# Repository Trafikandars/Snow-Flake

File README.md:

# Snow-Flake
Machine à Neige DMX pour le Theâtre - DMX Snow Flake Machine for theater

Ce projet vous est proposé par la compagnie Trafikandars :

C'est une machine permettant de lâcher des cotillons ou autre, contrôlable en DMX.
La construction nécessite des pièces imprimées en 3D et un circuit imprimé sur mesure. 
Tous les fichiers sont disponibles ici pour que vous puissiez la faire vous-même. 
Si vous n’avez pas le matériel nous vous proposons de vous envoyer un kit contenant tous les éléments nécessaire à son assemblage pour la monter ou de vous l’envoyer prête à l’usage.
Si vous trouvez des pistes d'améliorations je reste ouvert à toute requet : Trafikandars.workshop@gmail.com

Conception 3D : Adem Koanda_Saurel

Code : Côme Douville

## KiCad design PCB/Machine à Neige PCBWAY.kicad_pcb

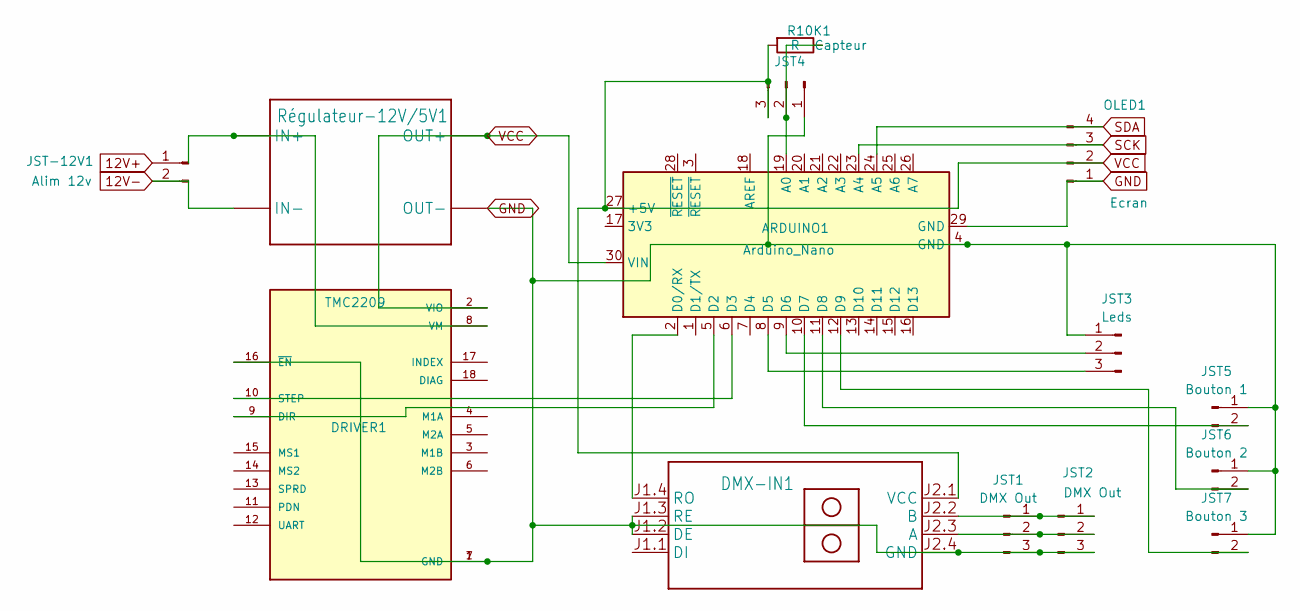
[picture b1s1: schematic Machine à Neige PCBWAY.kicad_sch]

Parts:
ARDUINO1: Arduino_Nano
DMX-IN1: RS485-TTL-CONVERTER
DRIVER1: TMC2209; MODULE_TMC2209_SILENTSTEPSTICK; PARTREV 1.20
JST1, JST2: DMX Out; PinSocket_1x03_P2.54mm_Vertical
JST3: Leds; PinSocket_1x03_P2.54mm_Vertical
JST4: Capteur; PinSocket_1x03_P2.54mm_Vertical
JST5: Bouton 1; PinSocket_1x02_P2.54mm_Vertical
JST6: Bouton 2; PinSocket_1x02_P2.54mm_Vertical
JST7: Bouton 3; PinSocket_1x02_P2.54mm_Vertical
JST-12V1: Alim 12v; PinSocket_1x02_P2.54mm_Vertical
OLED1: Ecran; PinSocket_1x04_P2.54mm_Vertical
R10K1: R; R_Axial_DIN0207_L6.3mm_D2.5mm_P5.08mm_Vertical
Régulateur-12V/5V1: StepDown-lm2596

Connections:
12V+: JST-12V1.1
12V-: JST-12V1.2, Régulateur-12V/5V1.2 (IN-)
GND: ARDUINO1.4 (GND), ARDUINO1.29 (GND), DMX-IN1.J1.2 (DE), DMX-IN1.J1.3 (RE), DMX-IN1.J2.4 (GND), DRIVER1.1 (GND), DRIVER1.7 (GND), DRIVER1.16 (~EN), JST1.3, JST2.3, JST3.1, JST4.1, JST5.1, JST6.1, JST7.1, OLED1.1, Régulateur-12V/5V1.4 (OUT-)
unnamed: ARDUINO1.19 (A0), JST4.2, R10K1.1
unnamed: ARDUINO1.2 (D0/RX), DMX-IN1.J1.4 (RO)
unnamed: ARDUINO1.5 (D2), DRIVER1.9 (DIR)
unnamed: ARDUINO1.6 (D3), DRIVER1.10 (STEP)
unnamed: ARDUINO1.8 (D5), JST3.3
unnamed: ARDUINO1.9 (D6), JST3.2
unnamed: ARDUINO1.10 (D7), JST5.2
unnamed: ARDUINO1.11 (D8), JST6.2
unnamed: ARDUINO1.12 (D9), JST7.2
unnamed: DMX-IN1.J2.3 (A), JST1.2, JST2.2
unnamed: DMX-IN1.J2.2 (B), JST1.1, JST2.1
unnamed: DRIVER1.8 (VM), Régulateur-12V/5V1.1 (IN+)
SCK: ARDUINO1.23 (A4), OLED1.3
SDA: ARDUINO1.24 (A5), OLED1.4
VCC: ARDUINO1.27 (+5V), ARDUINO1.30 (VIN), DMX-IN1.J2.1 (VCC), DRIVER1.2 (VIO), JST4.3, OLED1.2, R10K1.2, Régulateur-12V/5V1.3 (OUT+)

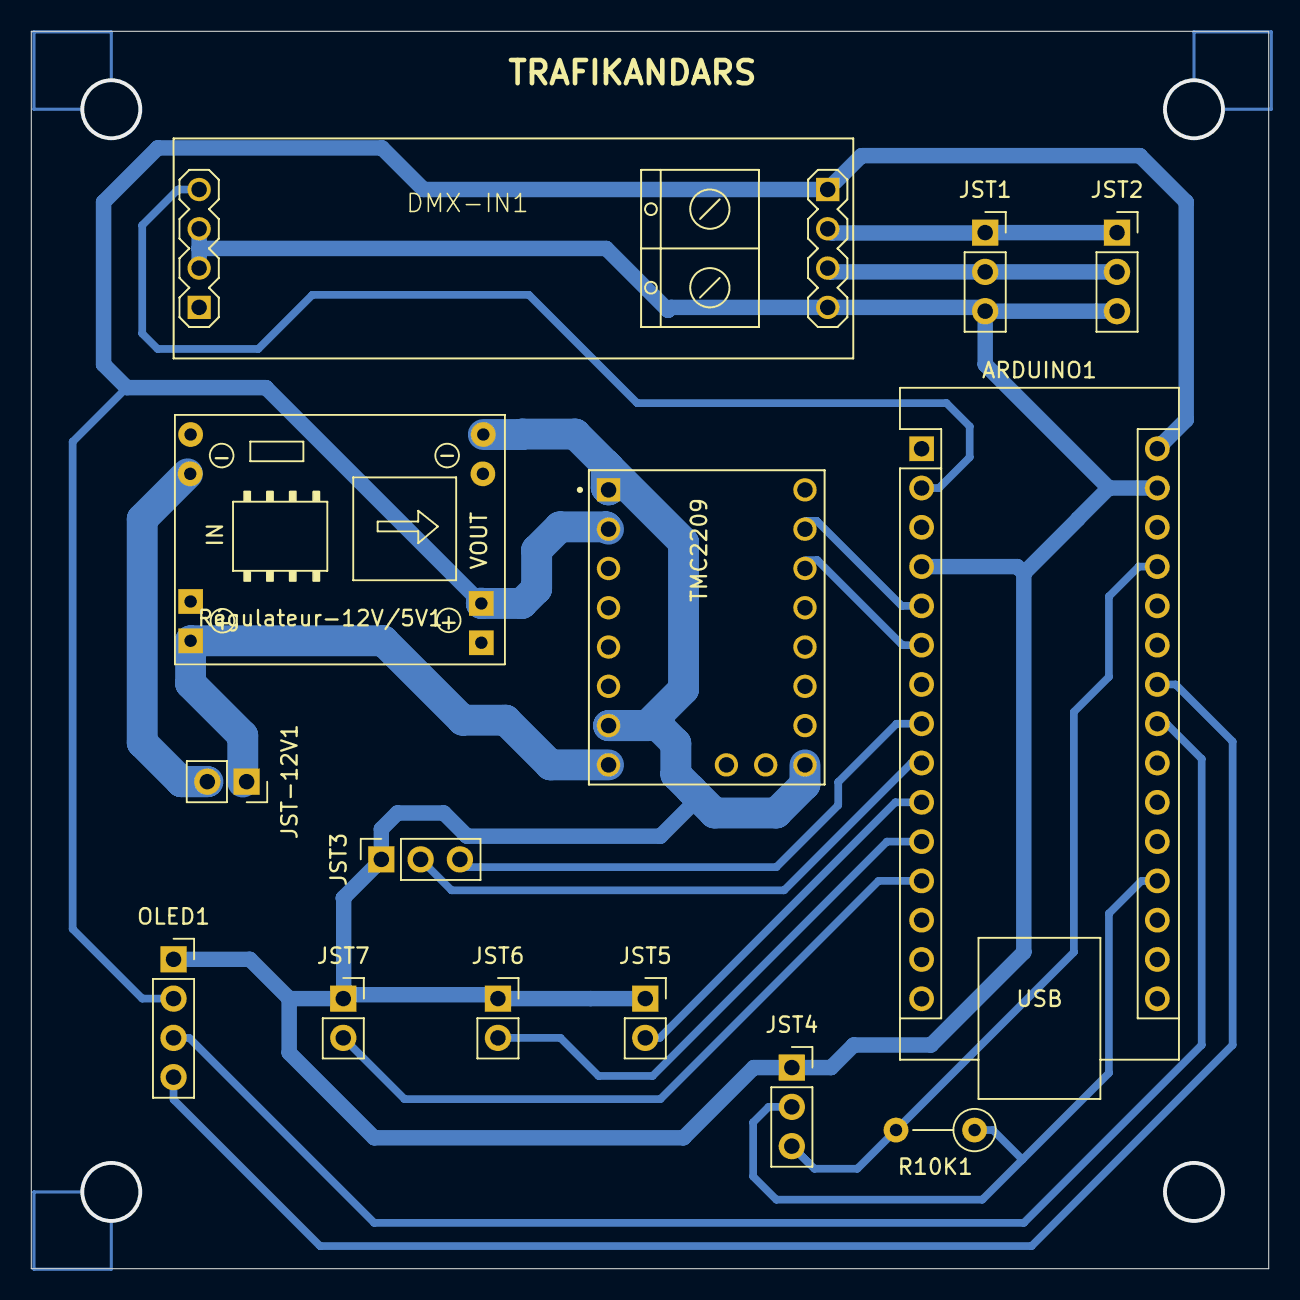
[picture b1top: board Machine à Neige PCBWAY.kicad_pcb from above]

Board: 2 copper layers, 80.0 x 80.0 mm, 14 parts (0 on the bottom side), 17 nets.

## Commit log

2026-04-29 Create 3d
2026-04-29 Create Arduino_Code
2026-04-29 Create PCB
2026-04-29 Update Montage
